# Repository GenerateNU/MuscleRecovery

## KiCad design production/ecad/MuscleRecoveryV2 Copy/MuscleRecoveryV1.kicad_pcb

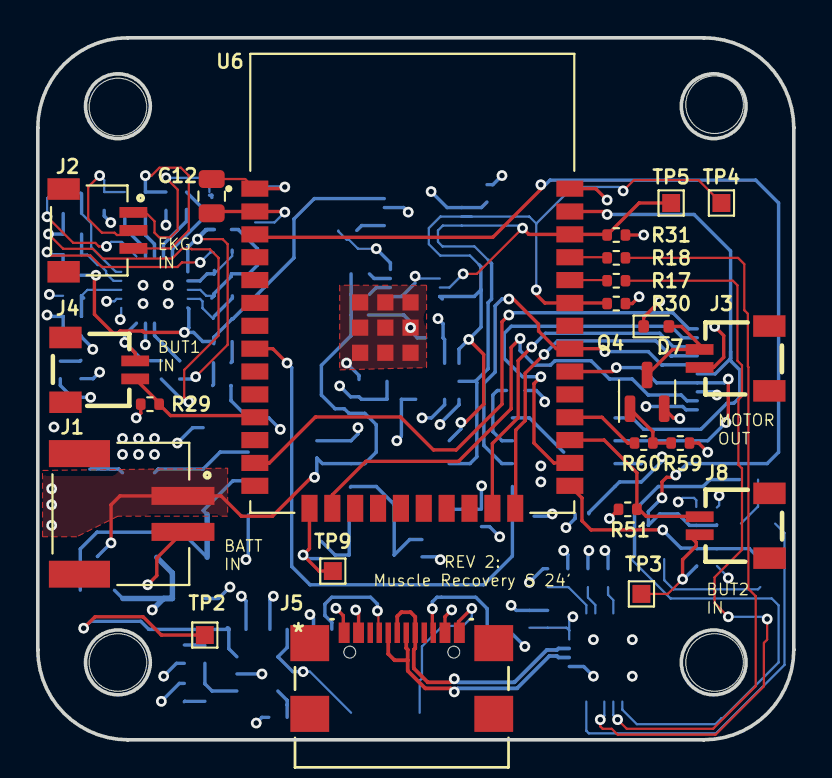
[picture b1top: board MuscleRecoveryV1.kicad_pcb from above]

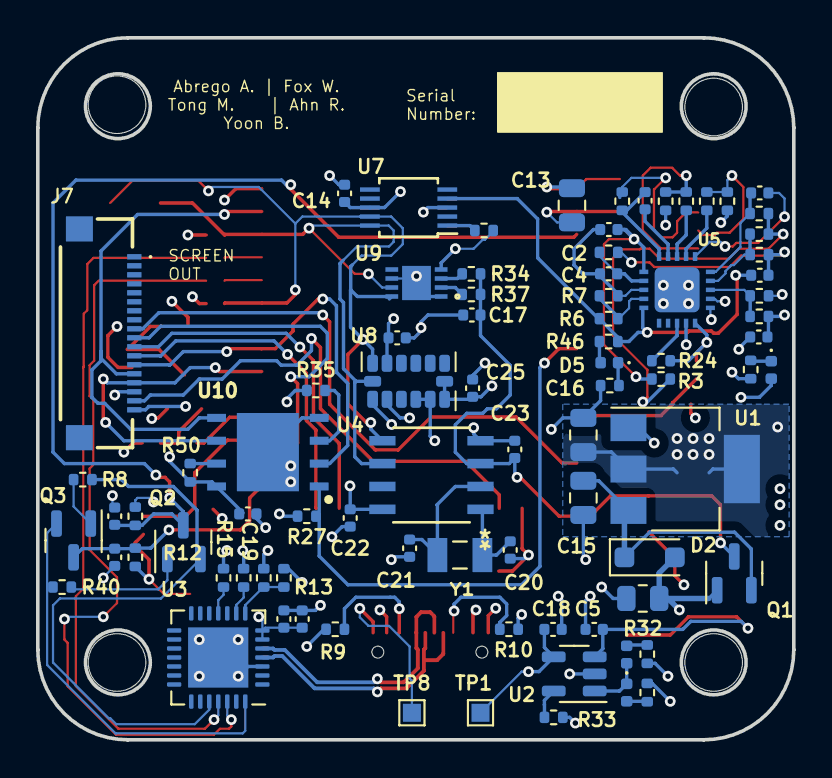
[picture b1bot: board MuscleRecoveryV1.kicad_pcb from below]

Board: 4 copper layers, 42.0 x 39.0 mm, 110 parts (83 on the bottom side), 71 nets.

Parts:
C1, C2: 470n; C_0402_1005Metric
C3: 270p; C_0402_1005Metric
C4, C10: 1n; C_0402_1005Metric
C5, C18: 10uF; C_0402_1005Metric
C6, C7: C_Small; C_0402_1005Metric
C8: 4.7uF; C_0402_1005Metric
C9: 100nF; C_0402_1005Metric
C11: 100n; C_0402_1005Metric
C12, C15, C16: 10uF; C_0805_2012Metric
C13: 1uF; C_0805_2012Metric
C14: 0.1u; C_0402_1005Metric
C17, C19, C22, C23, C24: 1uF; C_0402_1005Metric
C20, C21: 10pF; C_0402_1005Metric
C25: 0.1uF; C_0402_1005Metric
D2: MBR1020VL; D_SOD-123F
D3, D4: LED_Small; LED_0402_1005Metric
D5, D6: LED; LED_0402_1005Metric
D7: 1N914WT; D_SOD-523
H1, H2, H3, H4: MountingHole; MountingHole_3.2mm_M3
J1: S2B-PH-SM4-TB_LF__SN_; JST_S2B-PH-SM4-TB_LF__SN_
J2: SM03B-SRSS-TB_LF__SN_; JST_SM03B-SRSS-TB_LF__SN_
J3, J4, J8: SM02B-SRSS-TB_LF__SN_
J5: USB4110-GF-A; USB4110-GF-A_GCT
J7: 51296-1894; 512961894
Q1: FDN340P; SOT-23
Q2, Q3, Q4: AO3400A; SOT-23
R1, R2: 200k; R_0402_1005Metric
R3: 27k; R_0402_1005Metric
R4: 330k; R_0402_1005Metric
R5, R6, R25, R26: 1M; R_0402_1005Metric
R7: 100k; R_0402_1005Metric
R8, R15, R16, R27, R35, R40, R50: 10K; R_0402_1005Metric
R9, R10: 5.1K; R_0402_1005Metric
R11, R12: R_Small; R_0402_1005Metric
R13: 22.1K; R_0402_1005Metric
R14: 47.5K; R_0402_1005Metric
R17, R18, R24: 0; R_0402_1005Metric
R19, R22: 180K; R_0402_1005Metric
R20, R21: 2.2M; R_0402_1005Metric
R23: 390K; R_0402_1005Metric
R24#2: 1K; R_0402_1005Metric
R28: 180; R_0402_1005Metric
R29, R51, R59, R62: 10k; R_0402_1005Metric
R30, R31: 4.7k; R_0402_1005Metric
R32: 100k; R_0805_2012Metric
R33, R38, R39: 2K; R_0402_1005Metric
R34: 100; R_0402_1005Metric
R37, R46, R60: 1k; R_0402_1005Metric
TP1, TP2, TP3, TP4, TP5, TP8, TP9: TestPoint; TestPoint_Pad_1.0x1.0mm
U1: AP1117-33; SOT-223-3_TabPin2
U2: MCP73831-2-OT; SOT-23-5
U3: CP2102N-Axx-xQFN28; QFN-28-1EP_5x5mm_P0.5mm_EP3.35x3.35mm
U4: PCF8523T/1_118; SO8_SOT96-1_NXP
U5: AD8232ACPZ-R7; LFCSP_20
U6: ESP32-WROOM-32E__16MB_; XCVR_ESP32-WROOM-32E__16MB_
U7: ADS1115IDGS; TSSOP-10_3x3mm_P0.5mm
U8: ADXL343; LGA-14_3x5mm_P0.8mm_LayoutBorder1x6y
U9: MAX17043G+T; 21-0174B_MXM-L
U10: W25Q128JVPIQ; SON127P600X500X80-9N-D
Y1: ABS07-32.768KHZ-7-T; XTAL_ABS07-32.768KHZ-7-T

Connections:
+3V3: C8.1, C9.1, C11.1, C12.1, C13.1, C14.2, C16.1, C19.1, C22.1, C24.1, C25.1, D6.2 (A), D7.1 (K), J3.1, J4.1, J7.18, J8.1, R11.1, R12.1, R16.1, R20.2, R21.2, R24#2.1, R25.1, R27.1, R30.1, R31.2, R35.1, R50.1, TP3.1, U1.2 (VO), U3.6 (VDD), U3.7 (VREGIN), U4.8 (VDD), U5.15 (FR), U5.17 (VS+), U6.2 (VDD), U7.8 (VDD), U8.1 (Vdd_I/O), U8.6 (Vs), U8.7 (~CS), U8.12 (SDO/ADDR), U10.8 (VCC)
+BATT: C5.1, C17.1, C23.1, J1.1, Q1.3 (D), R34.1, R37.1, TP2.1, U2.3 (V_{BAT}), U4.3 (VBAT)
/Bootloading/DTR_Q: Q2.1 (G), R40.2
/Bootloading/RTS_Q: Q3.1 (G), R8.2
/Bootloading/RXD: R17.1, U3.26 (TXD)
/Bootloading/SUS_IN: R15.1, U3.11 (~SUSPEND)
/Bootloading/TXD: R18.1, U3.25 (RXD)
/Bootloading/VBUS_IN: R13.2, R14.1, U3.8 (VBUS)
ALT_START_BUTTON: J4.2, R29.1, U6.11 (IO26)
DTR: Q3.2 (S), R40.1, U3.28 (~DTR)
EN: C7.1, Q2.3 (D), R12.2, U6.3 (EN)
GND: C5.2, C6.2, C7.2, C8.2, C9.2, C11.2, C12.2, C13.2, C14.1, C15.2, C16.2, C17.2, C18.2, C19.2, C20.2, C21.2, C22.2, C23.2, C24.2, C25.2, J1.2, J5.A1-B12 (GND), J5.A12-B1 (GND), J7.16, Q4.2 (S), R9.2, R10.2, R14.2, R15.2, R24.2, R26.2, R28.2, R29.2, R32.2, R33.1, R39.1, R51.2, R59.2, R62.1, TP8.1, TP9.1, U1.1 (GND), U2.2 (V_{SS}), U3.3 (GND), U3.29 (GND), U4.4 (VSS), U5.14 (AC/*DC), U5.16 (GND), U5.GND, U6.1 (GND), U6.15 (GND), U6.38 (GND), U6.39_1 (GND), U6.39_2 (GND), U6.39_3 (GND), U6.39_4 (GND), U6.39_5 (GND), U6.39_6 (GND), U6.39_7 (GND), U6.39_8 (GND), U6.39_9 (GND), U7.3 (GND), U8.2 (GND), U8.4 (GND), U8.5 (GND), U9.1 (CTG), U9.4 (GND), U9.6 (QSRT), U9.9 (EPAD), U10.4 (GND_1), U10.9 (GND_2)
HP: R2.1, R4.1, U5.19 (IAOUT)
IO0: C6.1, Q3.3 (D), R11.2, U6.25 (IO0)
LA: J2.2, R19.1, R20.1
LIT: J7.17, U6.16 (IO13)
MISO: J7.13, U6.31 (IO19), U10.2 (DO_(IO1))
MOSI: J7.14, U6.37 (IO23), U10.5 (DI_(IO0))
MOTOR_EN: R60.1, U6.28 (IO17)
unnamed: C3.2, R4.2, R5.1
unnamed: C15.1, D2.1 (K), Q1.2 (S), U1.3 (VI)
unnamed: D3.2 (A), R38.2
unnamed: D3.1 (K), D4.2 (A), U2.1 (STAT)
unnamed: D4.1 (K), R39.2
unnamed: D5.2 (A), R46.2
unnamed: D5.1 (K), R24.1
unnamed: D6.1 (K), R28.1
unnamed: D7.2 (A), J3.2, Q4.3 (D)
unnamed: R50.2, U10.7 (~HOLD_OR_/RESET_(IO3))
unnamed: R35.2, U10.3 (~WP_(IO2))
unnamed: J5.A5 (CC1), R10.1
unnamed: J5.B5 (CC2), R9.1
unnamed: Q4.1 (G), R59.1, R60.2
unnamed: R1.2, R2.2, R3.1
unnamed: R33.2, U2.5 (PROG)
unnamed: R16.2, U3.9 (~RST)
unnamed: C1.1, U5.1 (HPDRIVE)
unnamed: C1.2, R1.1, U5.20 (HPSENSE)
unnamed: R19.2, U5.2 (IN+)
unnamed: R22.2, U5.3 (IN-)
unnamed: C4.2, R5.2, U5.7 (OPAMP+)
unnamed: R6.2, R7.2, U5.9 (OPAMP-)
unnamed: R25.2, R26.1, U5.18 (REFIN)
unnamed: C10.2, R23.2, U5.5 (RLD)
unnamed: C10.1, U5.4 (RLDFB)
unnamed: R62.2, U7.1 (ADDR)
unnamed: R37.2, U9.2 (CELL)
unnamed: R34.2, U9.3 (VDD)
OSC1: C20.1, U4.1 (OSCI), Y1.1
OSC2: C21.1, U4.2 (OSCO), Y1.2
RA: J2.3, R21.1, R22.1
REF: C2.2, C4.1, R7.1, U5.8 (REFOUT)
RL: J2.1, R23.1
RTS: Q2.2 (S), R8.1, U3.24 (~RTS)
RXD0: R17.2, U6.34 (RXD0)
SCK: J7.15, U6.30 (IO18), U10.6 (CLK)
SCL: R31.1, TP5.1, U4.6 (SCL), U6.36 (IO22), U7.10 (SCL), U8.14 (SCL/SCLK), U9.7 (SCL)
SDA: R30.2, TP4.1, U4.5 (SDA), U6.33 (IO21), U7.9 (SDA), U8.13 (SDA/SDI/SDIO), U9.8 (SDA)
SDN: R24#2.2, U5.13 (*SDN)
SD_CS: J7.9, U6.13 (IO14)
SPI_CS_FLSH: R27.2, U6.8 (IO32), U10.1 (~CS)
START_BUTTON: J8.2, R51.1, U6.27 (IO16)
SW: C2.1, R3.2, U5.6 (SW)
TFT_CS: J7.11, U6.23 (IO15)
TFT_DC: J7.12, U6.24 (IO2)
TFT_RST: J7.10, U6.26 (IO4)
TXD0: R18.2, U6.35 (TXD0)
USB+: J5.A7 (DN1), J5.B7 (DN2), U3.4 (D+)
USB-: J5.A6 (DP1), J5.B6 (DP2), U3.5 (D-)
VBUS: C18.1, D2.2 (A), J5.A4-B9 (VBUS), J5.A9-B4 (VBUS), Q1.1 (G), R13.1, R32.1, R38.1, TP1.1, U2.4 (V_{DD})
Vout: C3.1, R6.1, R46.1, U5.10 (OUT), U7.4 (AIN0)

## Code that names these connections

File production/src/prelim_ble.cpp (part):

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
/*
#if defined(ARDUINO_FEATHER_ESP32) // Feather Huzzah32
  #define TFT_CS         14
  #define TFT_RST        15
  #define TFT_DC         32

#elif defined(ESP8266)
  #define TFT_CS         4
  #define TFT_RST        16                                            
  #define TFT_DC         5

#else
  // For the breakout board, you can use any 2 or 3 pins.
  // These pins will also work for the 1.8" TFT shield.
  #define TFT_CS        10
  #define TFT_RST        9 // Or set to -1 and connect to Arduino RESET pin
  #define TFT_DC         8
#endif
*/

#define TFT_CS 15
#define TFT_RST 4
#define TFT_DC 2
#define TFT_MOSI 23  // Data out
#define TFT_SCLK 18  // Clock out

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
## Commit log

2024-01-22 Added Muscle Recovery schematics
2024-01-26 Added fuel guage schematic, may need adjustments
2024-01-31 Combined schematics together
2024-02-02 Starter web code
2024-02-02 Testing code upload for BLE
2024-02-02 Copied website somewhere in here contains the code we need to make our shit work
2024-02-04 add html code from PDR site
2024-02-05 changes to fuel guage schematic and quick draft of ecg schematic - not finished
2024-02-07 Testing Commit for Andy
2024-02-07 Pushing ESP-32 Implementation placed on the power page
2024-02-08 added ADS1115 schematic
2024-02-12 Sending data to website on button click
2024-02-12 cleaned up EMG
2024-02-12 Labels and other stuff
2024-02-13 Display commit 1
2024-02-13 Revert "Display commit 1"
    This reverts commit 52e50f7827ccbfa861bea7a8a003d131d02fed89.
2024-02-13 Display push attempt
2024-02-13 Display and Push Button
2024-02-13 rev1 first draft ready for review
2024-02-15 updates from Sean's comments, some not all
2024-02-16 inputting Sean's comments
2024-02-16 some emg changes
2024-02-17 Footprints added
2024-02-19 Maggie fixing her mistakes lol
2024-02-20 Adding Motor Circuitry
2024-02-22 updates to emg schematic from Alex and Sean suggestions
2024-02-22 Adding the Footprint + Symbol for the actual ESP Model we are going to use
2024-02-22 added libraries for both the symbols and footprint. Also added updated ESP-32 Symbol and footprint in the library
2024-02-23 updated footprints and emg schematic
2024-02-23 forgot the footprint for audio jack
2024-02-24 updated footprint assignments for ESP32 and S1-S4 to reference the folder Andy made
2024-02-25 supposedly finished schematic and footprints and started PCB
2024-02-25 Creating copy of folder for the final layout
2024-02-25 Created New Layout
2024-02-25 Adding the smaller button footprint
2024-02-25 Notifs work
2024-02-25 Pushing Layout Changes for Andy's Layout
2024-02-25 Commiting More Muscle Recovery V2 Changes
2024-02-26 Adding routing with the EKG routing included
2024-02-26 Committing My pliminary placement for my PCB <3
2024-02-26 Sending arrays of data
2024-02-27 Adding STEP file
2024-02-27 Functioning Data updating in graph render
2024-02-27 pushing current layout and other changes to be able to pull
2024-02-27 saving changes
2024-02-27 my first complete pcb draft
2024-02-28 Adding Folder w/ all of the 3D Step Models that are used in the board
2024-03-01 added accelerometer
2024-03-01 0 ohm resistors to acc
2024-03-01 final pcb updates
2024-03-01 extra save
2024-03-01 updated bom
2024-03-01 added accelerometer to layout
2024-03-25 Adding additional components to library for final rev2 changes
2024-03-25 Adding more updates to Rev2 Layout
2024-03-30 committing some recent changes to layout
2024-04-02 Pushing Most of the final changes for PCB REV2
2024-04-02 Pushing changes post schematic review
2024-04-03 Pushing final Rev2 PCBA Files
2024-04-03 Final Final FInal PCB
